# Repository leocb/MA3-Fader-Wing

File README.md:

# DIY GrandMA3 Fader Wing

An open source alternative hardware for the MA3 Fader wing. Intended for budget onPC setups.

This project should be:

- All electronic parts easily obtainable and be affordable
- 3D print everything
- easy to assemble

## Disclaimers ⚠️

> - **This project is a work in progress and is NOT ready yet!**
> - The project had a drastic change in direction, [read below](#explaining-the-project-changes) for more info.
> - This is a simple control surface that will send MIDI and/or OSC messages to the MA3 onPC software, it will **NOT** enable parameters on the MA3. If you need to enable parameters, the cheapest way to do it is by purchasing the MA3 2port Node with 4k parameters.
> - This project uses the GPL-3.0 license, which basically means that you can sell this if you want to, but any changes *must* be kept open source!

## Contributing 🤝

### Project contributions

- Feel free to open a PR with new features or bug fixes
- Use [KiCad 8](https://www.kicad.org/download/) or newer to open the PCB design files

### Financial support

Support this and more projects by donating:

## How to make your own 🚀

Coming soon™

I'm currently working on a prototype that should be ready in the near future.

## Parts List (NOT FINAL!)

- 15x Cherry MX compatible keyboard switches (and key caps)
- 5x Rotary knob with integrated push buttons (and knob caps)
- 5x Linear Fader (and fader caps)
- 20x 1n4148 Diode
- 15x 100nf Ceramic Capacitors
- ESP32 S2 mini
- 3D Printed enclosure and modules
- Lots of 30awg wire
- Perforated prototype PCB board

## PCB / Electronic Design ✏️

Coming soon™

## 3D Printed stuff

This control surface is intended to be fully 3D printed. Find the STL files [here](3D%20Print/)

If you want to make any modification to the models, these files were designed on OnShape (Free for non-commercial) [here](https://cad.onshape.com/documents/7848fe66a3315e098e2f40d5/w/8da4d24561bb0df992c0092a/e/0479437bc9edfbd2480cdb29)

## The code

Follow the code specific instructions [here](Code/README.md).

## Explaining the project changes

The initial intent behind this project was to make an affordable, DIY alternative for the MA3 command wing, having a custom PCB goes against the "affordable" part of it.

So, I've decided to remove the custom PCB entirely from this project and go with off the shelf parts. The previous iteration of this project is available on another git branch named `Legacy` in this same repository.

While the KiCad files in there are, in theory, ready for production, it has not been tested and the code for it has never been implemented. Feel free to use it however you like.

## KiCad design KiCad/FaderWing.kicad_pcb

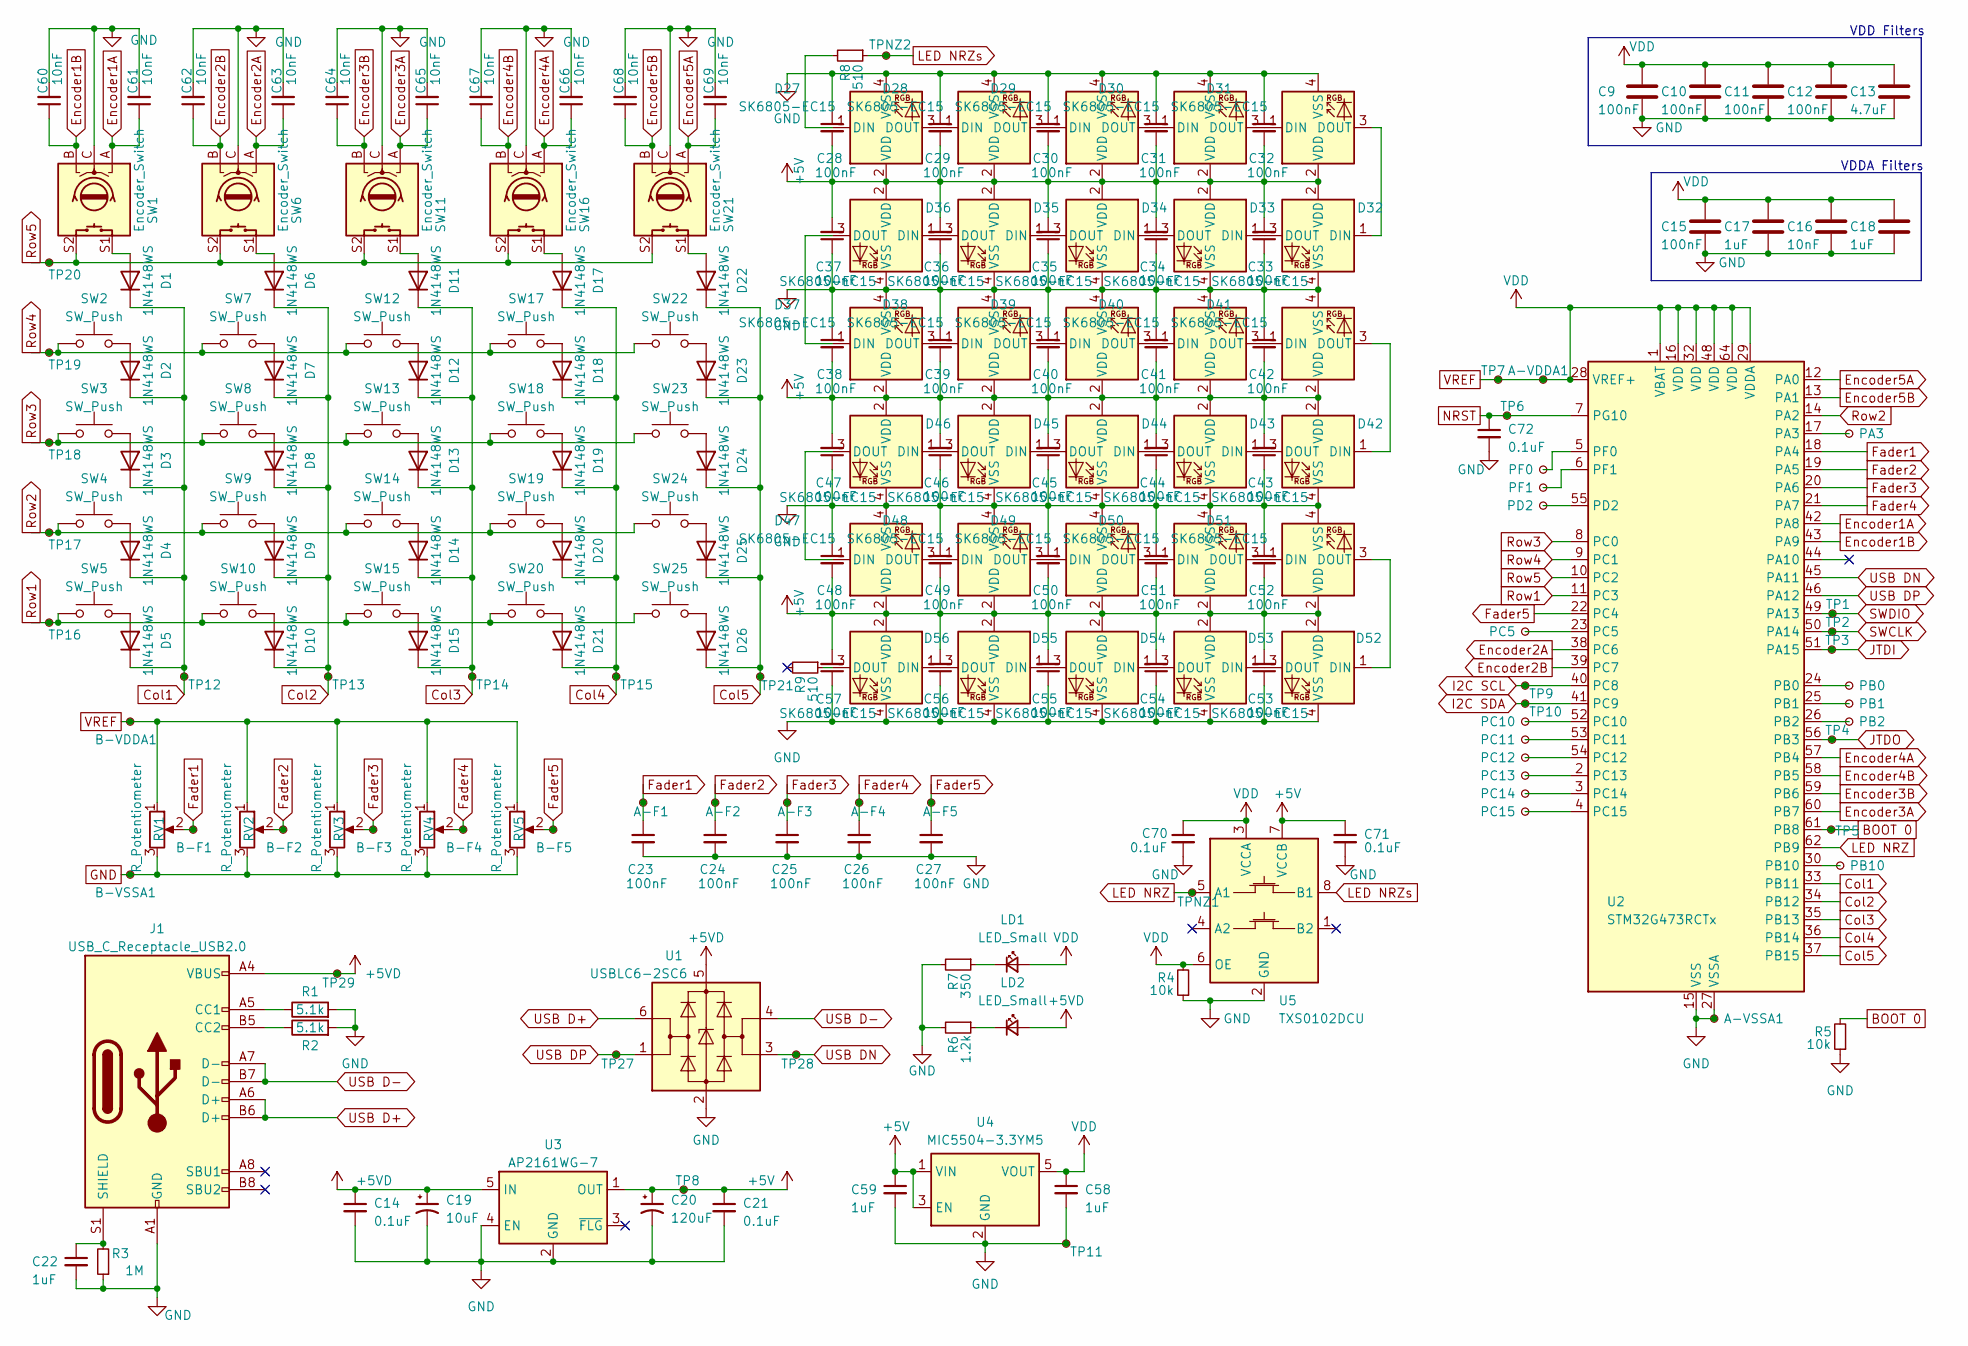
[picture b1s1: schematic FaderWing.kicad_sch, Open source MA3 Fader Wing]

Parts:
A-F1, A-F2, A-F3, A-F4, A-F5: TestPoint_Small; TestPoint_THTPad_D2.0mm_Drill1.0mm
A-VDDA1: TestPoint_Small; TestPoint_THTPad_D2.0mm_Drill1.0mm
A-VSSA1: TestPoint_Small; TestPoint_THTPad_D2.0mm_Drill1.0mm
B-F1, B-F2, B-F3, B-F4, B-F5: TestPoint_Small; TestPoint_THTPad_D2.0mm_Drill1.0mm
B-VDDA1: TestPoint_Small; TestPoint_THTPad_D2.0mm_Drill1.0mm
B-VSSA1: TestPoint_Small; TestPoint_THTPad_D2.0mm_Drill1.0mm
C9, C10, C11, C12, C15, C23, C24, C25, C26, C27, C28, C29, C30, C31, C32, C33, C34, C35, C36, C37, C38, C39, C40, C41, C42, C43, C44, C45, C46, C47, C48, C49, C50, C51, C52, C53, C54, C55, C56, C57: 100nF; C_0402_1005Metric
C13: 4.7uF; C_0603_1608Metric
C14, C21, C70, C71, C72: 0.1uF; C_0402_1005Metric
C16, C60, C61, C62, C63, C64, C65, C66, C67, C68, C69: 10nF; C_0402_1005Metric
C17, C18, C22, C58, C59: 1uF; C_0402_1005Metric
C19: 10uF; CP_EIA-3216-18_Kemet-A
C20: 120uF; CP_EIA-3528-21_Kemet-B
D1, D2, D3, D4, D5, D6, D7, D8, D9, D10, D11, D12, D13, D14, D15, D17, D18, D19, D20, D21, D22, D23, D24, D25, D26: 1N4148WS; D_SOD-323
D27, D28, D29, D30, D31, D32, D33, D34, D35, D36, D37, D38, D39, D40, D41, D42, D43, D44, D45, D46, D47, D48, D49, D50, D51, D52, D53, D54, D55, D56: SK6805-EC15; LED_SK6805_EC15_1.5x1.5mm
J1: USB_C_Receptacle_USB2.0; USB_C_Receptacle_GCT_USB4105-xx-A_16P_TopMnt_Horizontal
LD1, LD2: LED_Small; LED_1206_3216Metric
PA3: TestPoint_Small; TestPoint_Pad_D1.0mm
PB0, PB1, PB2, PB10: TestPoint_Small; TestPoint_Pad_D1.0mm
PC5, PC10, PC11, PC12, PC13, PC14, PC15: TestPoint_Small; TestPoint_Pad_D1.0mm
PD2: TestPoint_Small; TestPoint_Pad_D1.0mm
PF0, PF1: TestPoint_Small; TestPoint_Pad_D1.0mm
R1, R2: 5.1k; R_0603_1608Metric
R3: 1M; R_0603_1608Metric
R4, R5: 10k; R_0603_1608Metric
R6: 1.2k; R_0603_1608Metric
R7: 350; R_0603_1608Metric
R8, R9: 510; R_0603_1608Metric
RV1, RV2, RV3, RV4, RV5: R_Potentiometer; B103-75mm-Mixer-Fader-B10K
SW1, SW6, SW11, SW16, SW21: Encoder_Switch; RotaryEncoder_Alps_EC12E-Switch_Vertical_H20mm_CircularMoun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
SW2, SW3, SW4, SW5, SW7, SW8, SW9, SW10, SW12, SW13, SW14, SW15, SW17, SW18, SW19, SW20, SW22, SW23, SW24, SW25: SW_Push; SW_OUTEMU_1.00u_PCB_LED
TP1, TP2, TP3, TP4, TP5, TP6, TP7, TP8, TP9, TP10, TP11: TestPoint_Small; TestPoint_THTPad_D2.0mm_Drill1.0mm
TP12, TP13, TP14, TP15, TP16, TP17, TP18, TP19, TP20, TP21, TP27, TP28, TP29: TestPoint_Small; TestPoint_Pad_D1.0mm
TPNZ1, TPNZ2: TestPoint_Small; TestPoint_Pad_D1.0mm
U1: USBLC6-2SC6; SOT-23-6
U2: STM32G473RCTx; LQFP-64_10x10mm_P0.5mm
U3: AP2161WG-7; SOT-23-5
U4: MIC5504-3.3YM5; SOT-23-5
U5: TXS0102DCU; VSSOP-8_2.3x2mm_P0.5mm

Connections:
+5V: C20.1, C21.1, C28.2, C29.2, C30.2, C31.2, C32.2, C33.2, C34.2, C35.2, C36.2, C37.2, C38.2, C39.2, C40.2, C41.2, C42.2, C43.2, C44.2, C45.2, C46.2, C47.2, C48.2, C49.2, C50.2, C51.2, C52.2, C53.2, C54.2, C55.2, C56.2, C57.2, C59.1, C71.1, D27.2 (VDD), D28.2 (VDD), D29.2 (VDD), D30.2 (VDD), D31.2 (VDD), D32.2 (VDD), D33.2 (VDD), D34.2 (VDD), D35.2 (VDD), D36.2 (VDD), D37.2 (VDD), D38.2 (VDD), D39.2 (VDD), D40.2 (VDD), D41.2 (VDD), D42.2 (VDD), D43.2 (VDD), D44.2 (VDD), D45.2 (VDD), D46.2 (VDD), D47.2 (VDD), D48.2 (VDD), D49.2 (VDD), D50.2 (VDD), D51.2 (VDD), D52.2 (VDD), D53.2 (VDD), D54.2 (VDD), D55.2 (VDD), D56.2 (VDD), TP8.1, U3.1 (OUT), U4.1 (VIN), U4.3 (EN), U5.7 (VCCB)
+5VD: C14.1, C19.1, J1.A4 (VBUS), J1.A9 (VBUS), J1.B4 (VBUS), J1.B9 (VBUS), LD2.2 (A), TP29.1, U1.5 (VBUS), U3.5 (IN)
BOOT 0: R5.2, TP5.1, U2.61 (PB8)
Col1: D1.1 (K), D2.1 (K), D3.1 (K), D4.1 (K), D5.1 (K), TP12.1, U2.33 (PB11)
Col2: D6.1 (K), D7.1 (K), D8.1 (K), D9.1 (K), D10.1 (K), TP13.1, U2.34 (PB12)
Col3: D11.1 (K), D12.1 (K), D13.1 (K), D14.1 (K), D15.1 (K), TP14.1, U2.35 (PB13)
Col4: D17.1 (K), D18.1 (K), D19.1 (K), D20.1 (K), D21.1 (K), TP15.1, U2.36 (PB14)
Col5: D22.1 (K), D23.1 (K), D24.1 (K), D25.1 (K), D26.1 (K), TP21.1, U2.37 (PB15)
Encoder1A: C61.1, SW1.A, U2.42 (PA8)
Encoder1B: C60.1, SW1.B, U2.43 (PA9)
Encoder2A: C63.1, SW6.A, U2.38 (PC6)
Encoder2B: C62.1, SW6.B, U2.39 (PC7)
Encoder3A: C65.1, SW11.A, U2.60 (PB7)
Encoder3B: C64.1, SW11.B, U2.59 (PB6)
Encoder4A: C66.1, SW16.A, U2.57 (PB4)
Encoder4B: C67.1, SW16.B, U2.58 (PB5)
Encoder5A: C69.1, SW21.A, U2.12 (PA0)
Encoder5B: C68.1, SW21.B, U2.13 (PA1)
Fader1: A-F1.1, B-F1.1, C23.1, RV1.2, U2.18 (PA4)
Fader2: A-F2.1, B-F2.1, C24.1, RV2.2, U2.19 (PA5)
Fader3: A-F3.1, B-F3.1, C25.1, RV3.2, U2.20 (PA6)
Fader4: A-F4.1, B-F4.1, C26.1, RV4.2, U2.21 (PA7)
Fader5: A-F5.1, B-F5.1, C27.1, RV5.2, U2.22 (PC4)
GND: A-VSSA1.1, B-VSSA1.1, C9.2, C10.2, C11.2, C12.2, C13.2, C14.2, C15.2, C16.2, C17.2, C18.2, C19.2, C20.2, C21.2, C22.2, C23.2, C24.2, C25.2, C26.2, C27.2, C28.1, C29.1, C30.1, C31.1, C32.1, C33.1, C34.1, C35.1, C36.1, C37.1, C38.1, C39.1, C40.1, C41.1, C42.1, C43.1, C44.1, C45.1, C46.1, C47.1, C48.1, C49.1, C50.1, C51.1, C52.1, C53.1, C54.1, C55.1, C56.1, C57.1, C58.2, C59.2, C60.2, C61.2, C62.2, C63.2, C64.2, C65.2, C66.2, C67.2, C68.2, C69.2, C70.2, C71.2, C72.2, D27.4 (VSS), D28.4 (VSS), D29.4 (VSS), D30.4 (VSS), D31.4 (VSS), D32.4 (VSS), D33.4 (VSS), D34.4 (VSS), D35.4 (VSS), D36.4 (VSS), D37.4 (VSS), D38.4 (VSS), D39.4 (VSS), D40.4 (VSS), D41.4 (VSS), D42.4 (VSS), D43.4 (VSS), D44.4 (VSS), D45.4 (VSS), D46.4 (VSS), D47.4 (VSS), D48.4 (VSS), D49.4 (VSS), D50.4 (VSS), D51.4 (VSS), D52.4 (VSS), D53.4 (VSS), D54.4 (VSS), D55.4 (VSS), D56.4 (VSS), J1.A1 (GND), J1.A12 (GND), J1.B1 (GND), J1.B12 (GND), R1.2, R2.2, R3.1, R4.1, R5.1, R6.2, R7.2, RV1.3, RV2.3, RV3.3, RV4.3, RV5.3, SW1.C, SW6.C, SW11.C, SW16.C, SW21.C, TP11.1, U1.2 (GND), U2.15 (VSS), U2.27 (VSSA), U2.31 (VSS), U2.47 (VSS), U2.63 (VSS), U3.2 (GND), U3.4 (EN), U4.2 (GND), U5.2 (GND)
I2C SCL: TP9.1, U2.40 (PC8)
I2C SDA: TP10.1, U2.41 (PC9)
JTDI: TP3.1, U2.51 (PA15)
JTDO: TP4.1, U2.56 (PB3)
LED NRZ: TPNZ1.1, U2.62 (PB9), U5.5 (A1)
LED NRZs: R8.1, TPNZ2.1, U5.8 (B1)
NRST: C72.1, TP6.1, U2.7 (PG10)
unnamed: D1.2 (A), SW1.S1
unnamed: D2.2 (A), SW2.2
unnamed: D3.2 (A), SW3.2
unnamed: D4.2 (A), SW4.2
unnamed: D5.2 (A), SW5.2
unnamed: D6.2 (A), SW6.S1
unnamed: D7.2 (A), SW7.2
unnamed: D8.2 (A), SW8.2
unnamed: D9.2 (A), SW9.2
unnamed: D10.2 (A), SW10.2
unnamed: D11.2 (A), SW11.S1
unnamed: D12.2 (A), SW12.2
unnamed: D13.2 (A), SW13.2
unnamed: D14.2 (A), SW14.2
unnamed: D15.2 (A), SW15.2
unnamed: D17.2 (A), SW16.S1
unnamed: D18.2 (A), SW17.2
unnamed: D19.2 (A), SW18.2
unnamed: D20.2 (A), SW19.2
unnamed: D21.2 (A), SW20.2
unnamed: D22.2 (A), SW21.S1
unnamed: D23.2 (A), SW22.2
unnamed: D24.2 (A), SW23.2
unnamed: D25.2 (A), SW24.2
unnamed: D26.2 (A), SW25.2
unnamed: D27.1 (DIN), R8.2
unnamed: D27.3 (DOUT), D28.1 (DIN)
unnamed: D28.3 (DOUT), D29.1 (DIN)
unnamed: D29.3 (DOUT), D30.1 (DIN)
unnamed: D30.3 (DOUT), D31.1 (DIN)
unnamed: D31.3 (DOUT), D32.1 (DIN)
unnamed: D32.3 (DOUT), D33.1 (DIN)
unnamed: D33.3 (DOUT), D34.1 (DIN)
unnamed: D34.3 (DOUT), D35.1 (DIN)
unnamed: D35.3 (DOUT), D36.1 (DIN)
unnamed: D36.3 (DOUT), D37.1 (DIN)
unnamed: D37.3 (DOUT), D38.1 (DIN)
unnamed: D38.3 (DOUT), D39.1 (DIN)
unnamed: D39.3 (DOUT), D40.1 (DIN)
unnamed: D40.3 (DOUT), D41.1 (DIN)
unnamed: D41.3 (DOUT), D42.1 (DIN)
unnamed: D42.3 (DOUT), D43.1 (DIN)
unnamed: D43.3 (DOUT), D44.1 (DIN)
unnamed: D44.3 (DOUT), D45.1 (DIN)
unnamed: D45.3 (DOUT), D46.1 (DIN)
unnamed: D46.3 (DOUT), D47.1 (DIN)
unnamed: D47.3 (DOUT), D48.1 (DIN)
unnamed: D48.3 (DOUT), D49.1 (DIN)
unnamed: D49.3 (DOUT), D50.1 (DIN)
unnamed: D50.3 (DOUT), D51.1 (DIN)
unnamed: D51.3 (DOUT), D52.1 (DIN)
unnamed: D52.3 (DOUT), D53.1 (DIN)
unnamed: D53.3 (DOUT), D54.1 (DIN)
unnamed: D54.3 (DOUT), D55.1 (DIN)
unnamed: D55.3 (DOUT), D56.1 (DIN)
unnamed: D56.3 (DOUT), R9.1
unnamed: J1.A5 (CC1), R1.1
unnamed: J1.B5 (CC2), R2.1
unnamed: C22.1, J1.S1 (SHIELD), R3.2
unnamed: LD1.1 (K), R7.1
unnamed: LD2.1 (K), R6.1
unnamed: PA3.1, U2.17 (PA3)
unnamed: PB0.1, U2.24 (PB0)
unnamed: PB1.1, U2.25 (PB1)
unnamed: PB2.1, U2.26 (PB2)
unnamed: PB10.1, U2.30 (PB10)
unnamed: PC5.1, U2.23 (PC5)
unnamed: PC10.1, U2.52 (PC10)
unnamed: PC11.1, U2.53 (PC11)
unnamed: PC12.1, U2.54 (PC12)
unnamed: PC13.1, U2.2 (PC13)
unnamed: PC14.1, U2.3 (PC14)
unnamed: PC15.1, U2.4 (PC15)
unnamed: PD2.1, U2.55 (PD2)
unnamed: PF0.1, U2.5 (PF0)
unnamed: PF1.1, U2.6 (PF1)
Row1: SW5.1, SW10.1, SW15.1, SW20.1, SW25.1, TP16.1, U2.11 (PC3)
Row2: SW4.1, SW9.1, SW14.1, SW19.1, SW24.1, TP17.1, U2.14 (PA2)
Row3: SW3.1, SW8.1, SW13.1, SW18.1, SW23.1, TP18.1, U2.8 (PC0)
Row4: SW2.1, SW7.1, SW12.1, SW17.1, SW22.1, TP19.1, U2.9 (PC1)
Row5: SW1.S2, SW6.S2, SW11.S2, SW16.S2, SW21.S2, TP20.1, U2.10 (PC2)
SWCLK: TP2.1, U2.50 (PA14)
SWDIO: TP1.1, U2.49 (PA13)
USB D+: J1.A6 (D+), J1.B6 (D+), U1.6 (I/O1)
USB D-: J1.A7 (D-), J1.B7 (D-), U1.4 (I/O2)
USB DN: TP28.1, U1.3 (I/O2), U2.45 (PA11)
USB DP: TP27.1, U1.1 (I/O1), U2.46 (PA12)
VREF: A-VDDA1.1, B-VDDA1.1, C9.1, C10.1, C11.1, C12.1, C13.1, C15.1, C16.1, C17.1, C18.1, C58.1, C70.1, LD1.2 (A), R4.2, RV1.1, RV2.1, RV3.1, RV4.1, RV5.1, TP7.1, U2.1 (VBAT), U2.16 (VDD), U2.28 (VREF+), U2.29 (VDDA), U2.32 (VDD), U2.48 (VDD), U2.64 (VDD), U4.5 (VOUT), U5.3 (VCCA), U5.6 (OE)

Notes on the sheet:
VDDA Filters
VDD Filters

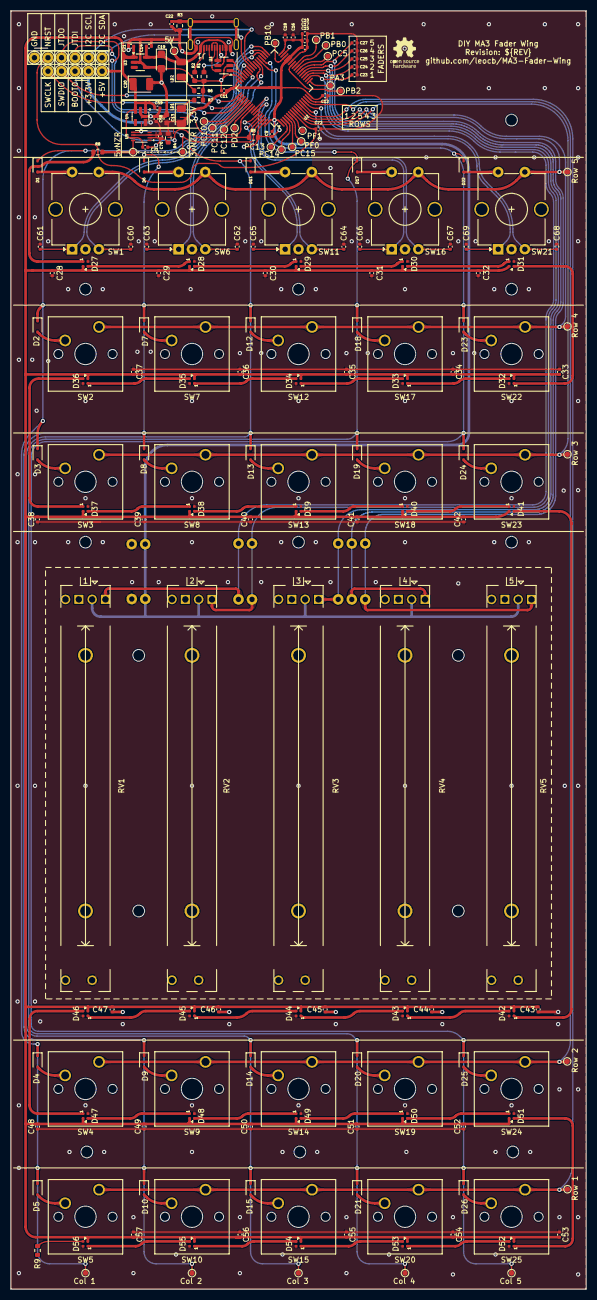
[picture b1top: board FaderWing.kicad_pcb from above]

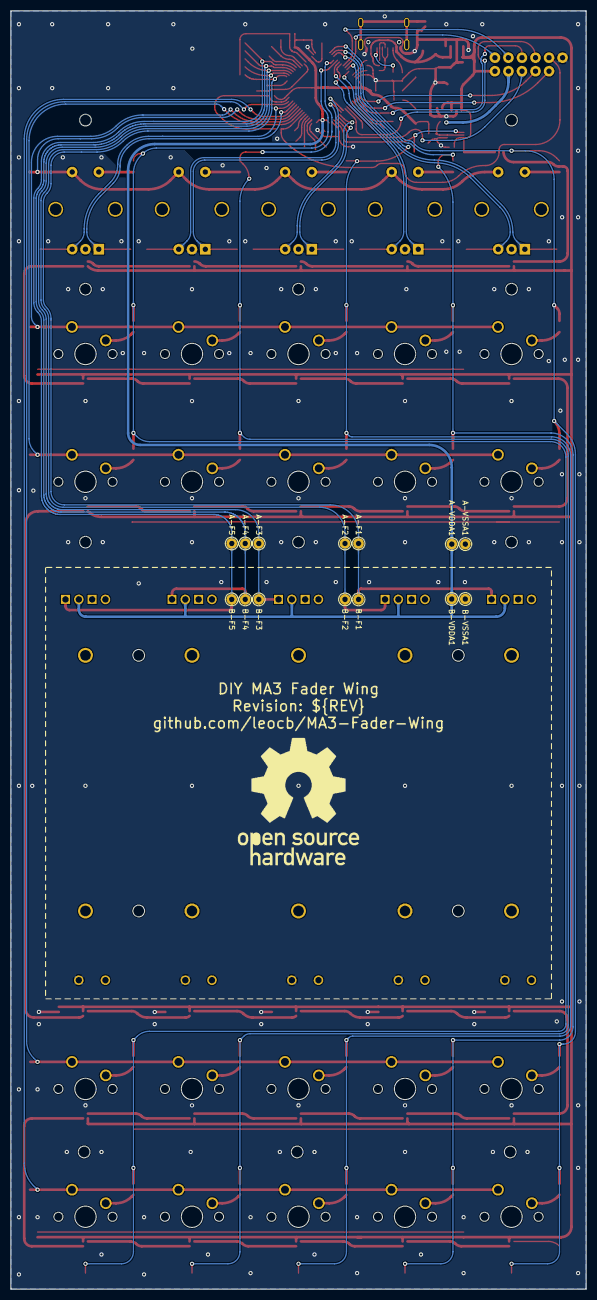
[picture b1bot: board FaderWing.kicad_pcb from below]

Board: 2 copper layers, 108.0 x 240.0 mm, 219 parts (14 on the bottom side), 119 nets.

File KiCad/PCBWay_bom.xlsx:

|  |  | xxxx xxxx xxxxx xxPCS BOM (Sample Bill of Materials)
Item # | *Designator | *Qty | Manufacturer | *Mfg Part # | Description / Value | *Package/Footprint | Type | Your Instructions / Notes
1 | C10, C11, C12, C15, C23, C24, C25, C26, C27, C28, C29, C30, C31, C32, C33, C34,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 | 40 | KEMET | C0402C104K4RACTU | Capacitor 100nF (0.1uF) Ceramic | C_0402_1005Metric | SMD | If needed, every item in this list is allowed to be replaced by equivalent comp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
2 | C13 | 1 | KEMET | C0603C475K9PACTU | Capacitor 4.7uF Ceramic | C_0603_1608Metric | SMD | All capacitors in this list must be able to hande 5V or more
3 | C14, C21, C70, C71, C72 | 5 | KEMET | C0402C104K4RACTU | Capacitor 0.1uF Ceramic | C_0402_1005Metric | SMD
4 | C16, C60, C61, C62, C63, C64, C65, C66, C67, C68, C69 | 11 | KEMET | C0402C103K9PACTU | Capacitor 10nF (0.01uF) Ceramic | C_0402_1005Metric | SMD
5 | C17, C18, C22, C58, C59 | 5 | KEMET | C0402C105K8PACTU | Capacitor 1uF Ceramic | C_0402_1005Metric | SMD
6 | C19 | 1 | KEMET | T520A106M010ATE080 | Capacitor 10uF Tantalum | CP_EIA-3216-18_Kemet-A | SMD
7 | C20 | 1 | KEMET | T520B127M006ATE035 | Capacitor 120uF Tantalum | CP_EIA-3528-21_Kemet-B | SMD
8 | D1, D10, D11, D12, D13, D14, D15, D17, D18, D19, D2, D20, D21, D22, D23, D24, D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 | 25 | Vishay Semiconductors | 1N4148WS-HE3-18 | Diode / 1N4148WS | D_SOD-323 | SMD
9 | D27, D28, D29, D30, D31, D32, D33, D34, D35, D36, D37, D38, D39, D40, D41, D42,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 | 30 | Adafruit | 4492 | LED / SK6805-EC15 | LED_SK6805_EC15_1.5x1.5mm | SMD | Maybe these LEDs are too expensive, please verify lowest price
10 | J1 | 1 | GCT | USB4105-GF-A | USB_C_Receptacle_USB2.0 | USB_C_Receptacle_GCT_USB4105-xx-A_16P_TopMnt_Horizontal | SMD
11 | LD1, LD2 | 2 | Kingbright | APT3216LZGCK | Small LED Green | LED_1206_3216Metric | SMD
12 | R1, R2 | 2 | Panasonic | ERJ-3EKF5101V | Resistor 5.1k Ohm | R_0603_1608Metric | SMD
13 | R3 | 1 | Panasonic | ERJ-3EKF1004V | Resistor 1M Ohm | R_0603_1608Metric | SMD
14 | R4, R5 | 2 | Panasonic | ERJ-3EKF1002V | Resistor 10k Ohm | R_0603_1608Metric | SMD
15 | R6 | 1 | Panasonic | ERJ-3EKF6800V | Resistor 680 Ohm | R_0603_1608Metric | SMD
16 | R7 | 1 | Panasonic | ERJ-3EKF3000V | Resistor 300 Ohm | R_0603_1608Metric | SMD
17 | R8, R9 | 2 | Panasonic | ERJ-3EKF5100V | Resistor 510 Ohm | R_0603_1608Metric | SMD
18 | U1 | 1 | STMicroelectronics | USBLC6-2SC6 | USBLC6-2SC6 | SOT-23-6 | SMD
19 | U2 | 1 | STMicroelectronics | STM32G473RCT6 | STM32G473RCTx | LQFP-64_10x10mm_P0.5mm | SMD
20 | U3 | 1 | Diodes Incorporated | AP2161WG-7 | AP2161WG-7 | SOT-23-5 | SMD
21 | U4 | 1 | Microchip Technology | MIC5504-3.3YM5-TR | MIC5504-3.3YM5 | SOT-23-5 | SMD
22 | U5 | 1 | Texas Instruments | TXS0102DCUR | TXS0102DCU | VSSOP-8_2.3x2mm_P0.5mm | SMD
Need a quick and accurante quote? Need an efficient production? Please read SMT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
Click for Instructions on How to Create a BOM

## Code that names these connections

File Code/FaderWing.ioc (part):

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Mcu.Name=STM32G473R(B-C-E)Tx
Mcu.Package=LQFP64
Mcu.UserName=STM32G473RCTx
PA0.GPIOParameters=GPIO_Speed,GPIO_PuPd,GPIO_Label
PA0.GPIO_Label=Enc5A
PA0.GPIO_PuPd=GPIO_PULLUP
PA0.GPIO_Speed=GPIO_SPEED_FREQ_MEDIUM
PA0.Signal=S_TIM5_CH1
PA1.GPIOParameters=GPIO_Speed,GPIO_PuPd,GPIO_Label
PA1.GPIO_Label=Enc5B
PA1.GPIO_PuPd=GPIO_PULLUP
PA1.GPIO_Speed=GPIO_SPEED_FREQ_MEDIUM
PA1.Signal=S_TIM5_CH2
PA11.Mode=Device
PA11.Signal=USB_DM
PA12.Mode=Device
PA12.Signal=USB_DP
PA13.Mode=JTAG_4_pins
PA13.Signal=SYS_JTMS-SWDIO
PA14.Mode=JTAG_4_pins
PA14.Signal=SYS_JTCK-SWCLK
PA15.Mode=JTAG_4_pins
PA15.Signal=SYS_JTDI
PA2.GPIOParameters=GPIO_Speed,GPIO_Label
PA2.GPIO_Label=Row2
PA2.GPIO_Speed=GPIO_SPEED_FREQ_HIGH
PA2.Signal=GPIO_Output
PA4.GPIOParameters=GPIO_Label
PA4.GPIO_Label=F1
PA4.Mode=IN17-Single-Ended
PA4.Signal=ADC2_IN17
PA5.GPIOParameters=GPIO_Label
PA5.GPIO_Label=F2
PA5.Mode=IN13-Single-Ended
PA5.Signal=ADC2_IN13
PA6.GPIOParameters=GPIO_Label
PA6.GPIO_Label=F3
PA6.Mode=IN3-Single-Ended
PA6.Signal=ADC2_IN3
PA7.GPIOParameters=GPIO_Label
PA7.GPIO_Label=F4
PA7.Mode=IN4-Single-Ended
PA7.Signal=ADC2_IN4
PA8.GPIOParameters=GPIO_Speed,GPIO_PuPd,GPIO_Label
PA8.GPIO_Label=Enc1A
PA8.GPIO_PuPd=GPIO_PULLUP
PA8.GPIO_Speed=GPIO_SPEED_FREQ_MEDIUM
PA8.Signal=S_TIM1_CH1
PA9.GPIOParameters=GPIO_Speed,GPIO_PuPd,GPIO_Label
PA9.GPIO_Label=Enc1B
PA9.GPIO_PuPd=GPIO_PULLUP
PA9.GPIO_Speed=GPIO_SPEED_FREQ_MEDIUM
PA9.Signal=S_TIM1_CH2
PB11.GPIOParameters=GPIO_PuPd,GPIO_Label
PB11.GPIO_Label=Col1
PB11.GPIO_PuPd=GPIO_PULLDOWN
PB11.Signal=GPIO_Input
PB12.GPIOParameters=GPIO_PuPd,GPIO_Label
PB12.GPIO_Label=Col2
PB12.GPIO_PuPd=GPIO_PULLDOWN
PB12.Signal=GPIO_Input
PB13.GPIOParameters=GPIO_PuPd,GPIO_Label
PB13.GPIO_Label=Col3
PB13.GPIO_PuPd=GPIO_PULLDOWN
PB13.Signal=GPIO_Input
PB14.GPIOParameters=GPIO_PuPd,GPIO_Label
PB14.GPIO_Label=Col4
PB14.GPIO_PuPd=GPIO_PULLDOWN
PB14.Signal=GPIO_Input
PB15.GPIOParameters=GPIO_PuPd,GPIO_Label
PB15.GPIO_Label=Col5
PB15.GPIO_PuPd=GPIO_PULLDOWN
PB15.Signal=GPIO_Input
PB3.Mode=JTAG_4_pins
PB3.Signal=SYS_JTDO-SWO
PB4.GPIOParameters=GPIO_Speed,GPIO_PuPd,GPIO_Label
PB4.GPIO_Label=Enc4A
PB4.GPIO_PuPd=GPIO_PULLUP
PB4.GPIO_Speed=GPIO_SPEED_FREQ_MEDIUM
PB4.Signal=S_TIM3_CH1
PB5.GPIOParameters=GPIO_Speed,GPIO_PuPd,GPIO_Label
PB5.GPIO_Label=Enc4B
PB5.GPIO_PuPd=GPIO_PULLUP
PB5.GPIO_Speed=GPIO_SPEED_FREQ_MEDIUM
PB5.Signal=S_TIM3_CH2
PB6.GPIOParameters=GPIO_Speed,GPIO_PuPd,GPIO_Label
PB6.GPIO_Label=Enc3A
PB6.GPIO_PuPd=GPIO_PULLUP
PB6.GPIO_Speed=GPIO_SPEED_FREQ_MEDIUM
PB6.Signal=S_TIM4_CH1
PB7.GPIOParameters=GPIO_Speed,GPIO_PuPd,GPIO_Label
PB7.GPIO_Label=Enc3B
PB7.GPIO_PuPd=GPIO_PULLUP
PB7.GPIO_Speed=GPIO_SPEED_FREQ_MEDIUM
PB7.Signal=S_TIM4_CH2
PB9.GPIOParameters=GPIO_Label
PB9.GPIO_Label=LED NZR
PB9.Signal=S_TIM4_CH4
PC0.GPIOParameters=GPIO_Speed,GPIO_Label
PC0.GPIO_Label=Row3
PC0.GPIO_Speed=GPIO_SPEED_FREQ_HIGH
PC0.Signal=GPIO_Output
PC1.GPIOParameters=GPIO_Speed,GPIO_Label
PC1.GPIO_Label=Row4
PC1.GPIO_Speed=GPIO_SPEED_FREQ_HIGH
PC1.Signal=GPIO_Output
PC2.GPIOParameters=GPIO_Speed,GPIO_Label
PC2.GPIO_Label=Row5
PC2.GPIO_Speed=GPIO_SPEED_FREQ_HIGH
PC2.Signal=GPIO_Output
PC3.GPIOParameters=GPIO_Speed,PinState,GPIO_Label
PC3.GPIO_Label=Row1
PC3.GPIO_Speed=GPIO_SPEED_FREQ_HIGH
PC3.PinState=GPIO_PIN_RESET
PC3.Signal=GPIO_Output
PC4.GPIOParameters=GPIO_Label
PC4.GPIO_Label=F5
PC4.Mode=IN5-Single-Ended
PC4.Signal=ADC2_IN5
PC6.GPIOParameters=GPIO_Speed,GPIO_PuPd,GPIO_Label
PC6.GPIO_Label=Enc2A
PC6.GPIO_PuPd=GPIO_PULLUP
PC6.GPIO_Speed=GPIO_SPEED_FREQ_MEDIUM
PC6.Signal=S_TIM8_CH1
PC7.GPIOParameters=GPIO_Speed,GPIO_PuPd,GPIO_Label
PC7.GPIO_Label=Enc2B
PC7.GPIO_PuPd=GPIO_PULLUP
PC7.GPIO_Speed=GPIO_SPEED_FREQ_MEDIUM
PC7.Signal=S_TIM8_CH2
PC8.Mode=I2C
PC8.Signal=I2C3_SCL
PC9.Mode=I2C
PC9.Signal=I2C3_SDA
RCC.HSE_VALUE=48000000
RCC.SYSCLKFreq_VALUE=150000000
RCC.SYSCLKSource=RCC_SYSCLKSOURCE_PLLCLK
board=custom

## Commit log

2023-02-16 Add KiCad Files
2023-02-16 Add basic STM32 Cube files
2023-02-16 Fix readme images
2023-02-16 update with kicad info
2023-02-16 Add KiCad custom footprints
2023-02-16 Update readme with kicad download link
2023-02-23 PCB Revision 0.5
2023-04-13 add work in progress disclaimer in readme
2023-04-13 add ma3 parameters disclaimer on readme
2023-04-13 add gpl 3 license disclaimer
2024-05-08 Update to V1.0
    This is what I would consider as ready for fabrication
    + Power LEDs
    ~ Revised SK6805-EC15 footprints
    + (removeable) Series NZR protection 500Ohm resistor
    ~ Moved USB port and PSU to the left to shorten the USB traces
    ~ Update project to KiCad 8
2024-05-09 Improve components routing
2024-05-10 Update Images
2024-05-10 Fix some labels
2024-05-11 Update components to use less dumb packages
2024-05-17 Files to order on PCBway, Revised
2024-05-29 Fix 5v LED resistor
2024-05-29 Update BOM
2024-10-08 Remove cutout in the middle of the board to reduce costs (custom panelling)
2025-01-01 Remove Legacy stuff
2025-01-01 Add code readme
2025-01-01 Add 3D printed enclosure
2025-01-01 Update Readme with 3d print info
2025-01-02 I changed my mind, we using arduino IDE now
2025-01-02 Prototype HID testing
2025-01-02 Add useful link
2025-01-02 github is stupid
2025-01-03 Add Rider-Avalonia base project
2025-01-06 Add Device images
2025-01-06 Update Device Images
2025-01-06 Update Device Tick marks
2025-01-06 Update UI Model blender file with fader shadow compositor nodes
2025-01-06 Force Light mode
2025-01-06 Device Button View User Control
2025-01-06 sure why not
2025-01-06 Basic Device View
2025-01-06 no resize for you
2025-01-12 Update Device visuals
2025-01-12 Device Views done
2025-01-13 Enable easier test
2025-01-13 Add HidSharp, ObjectDumper
2025-01-13 Fix User Control Bindings
2025-01-13 Basic Device HID Control
2025-01-13 Remove unused usings
2025-01-18 Use AdaFruit Tiny USB, Set Manufacturer, Product and Serial Descriptors
2025-01-18 Support for automatic connection to HID given a serial number
2025-01-18 Fix: Ignore USB Descriptors with errors.
